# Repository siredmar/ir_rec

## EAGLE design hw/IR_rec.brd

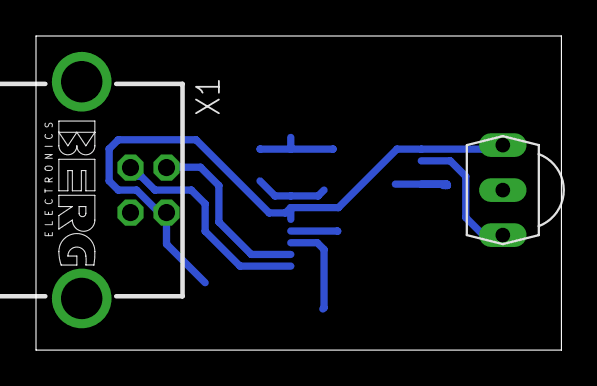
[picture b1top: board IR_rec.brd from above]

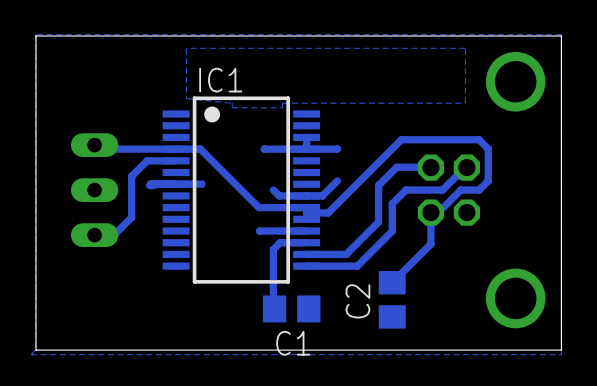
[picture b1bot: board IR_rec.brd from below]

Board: 2 copper layers, 29.2 x 17.4 mm, 5 parts (3 on the bottom side), 6 nets.

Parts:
C1, C2: 100n; C0805
IC1: FT232RL; SSOP28
U$1: TSOP1836; TSOP18XX
X1: PN61729-S

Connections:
+5V: C2.2, IC1.4, IC1.19, IC1.20, U$1.VCC, X1.1
GND: C1.1, C2.1, IC1.7, IC1.18, IC1.21, IC1.25, IC1.26, U$1.GND, X1.4, X1.S1, X1.S2
unnamed: C1.2, IC1.17
OUT: IC1.5, U$1.OUT
USBDM: IC1.16, X1.2
USBDP: IC1.15, X1.3

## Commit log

2014-10-17 added IR_rec sch/brd files
